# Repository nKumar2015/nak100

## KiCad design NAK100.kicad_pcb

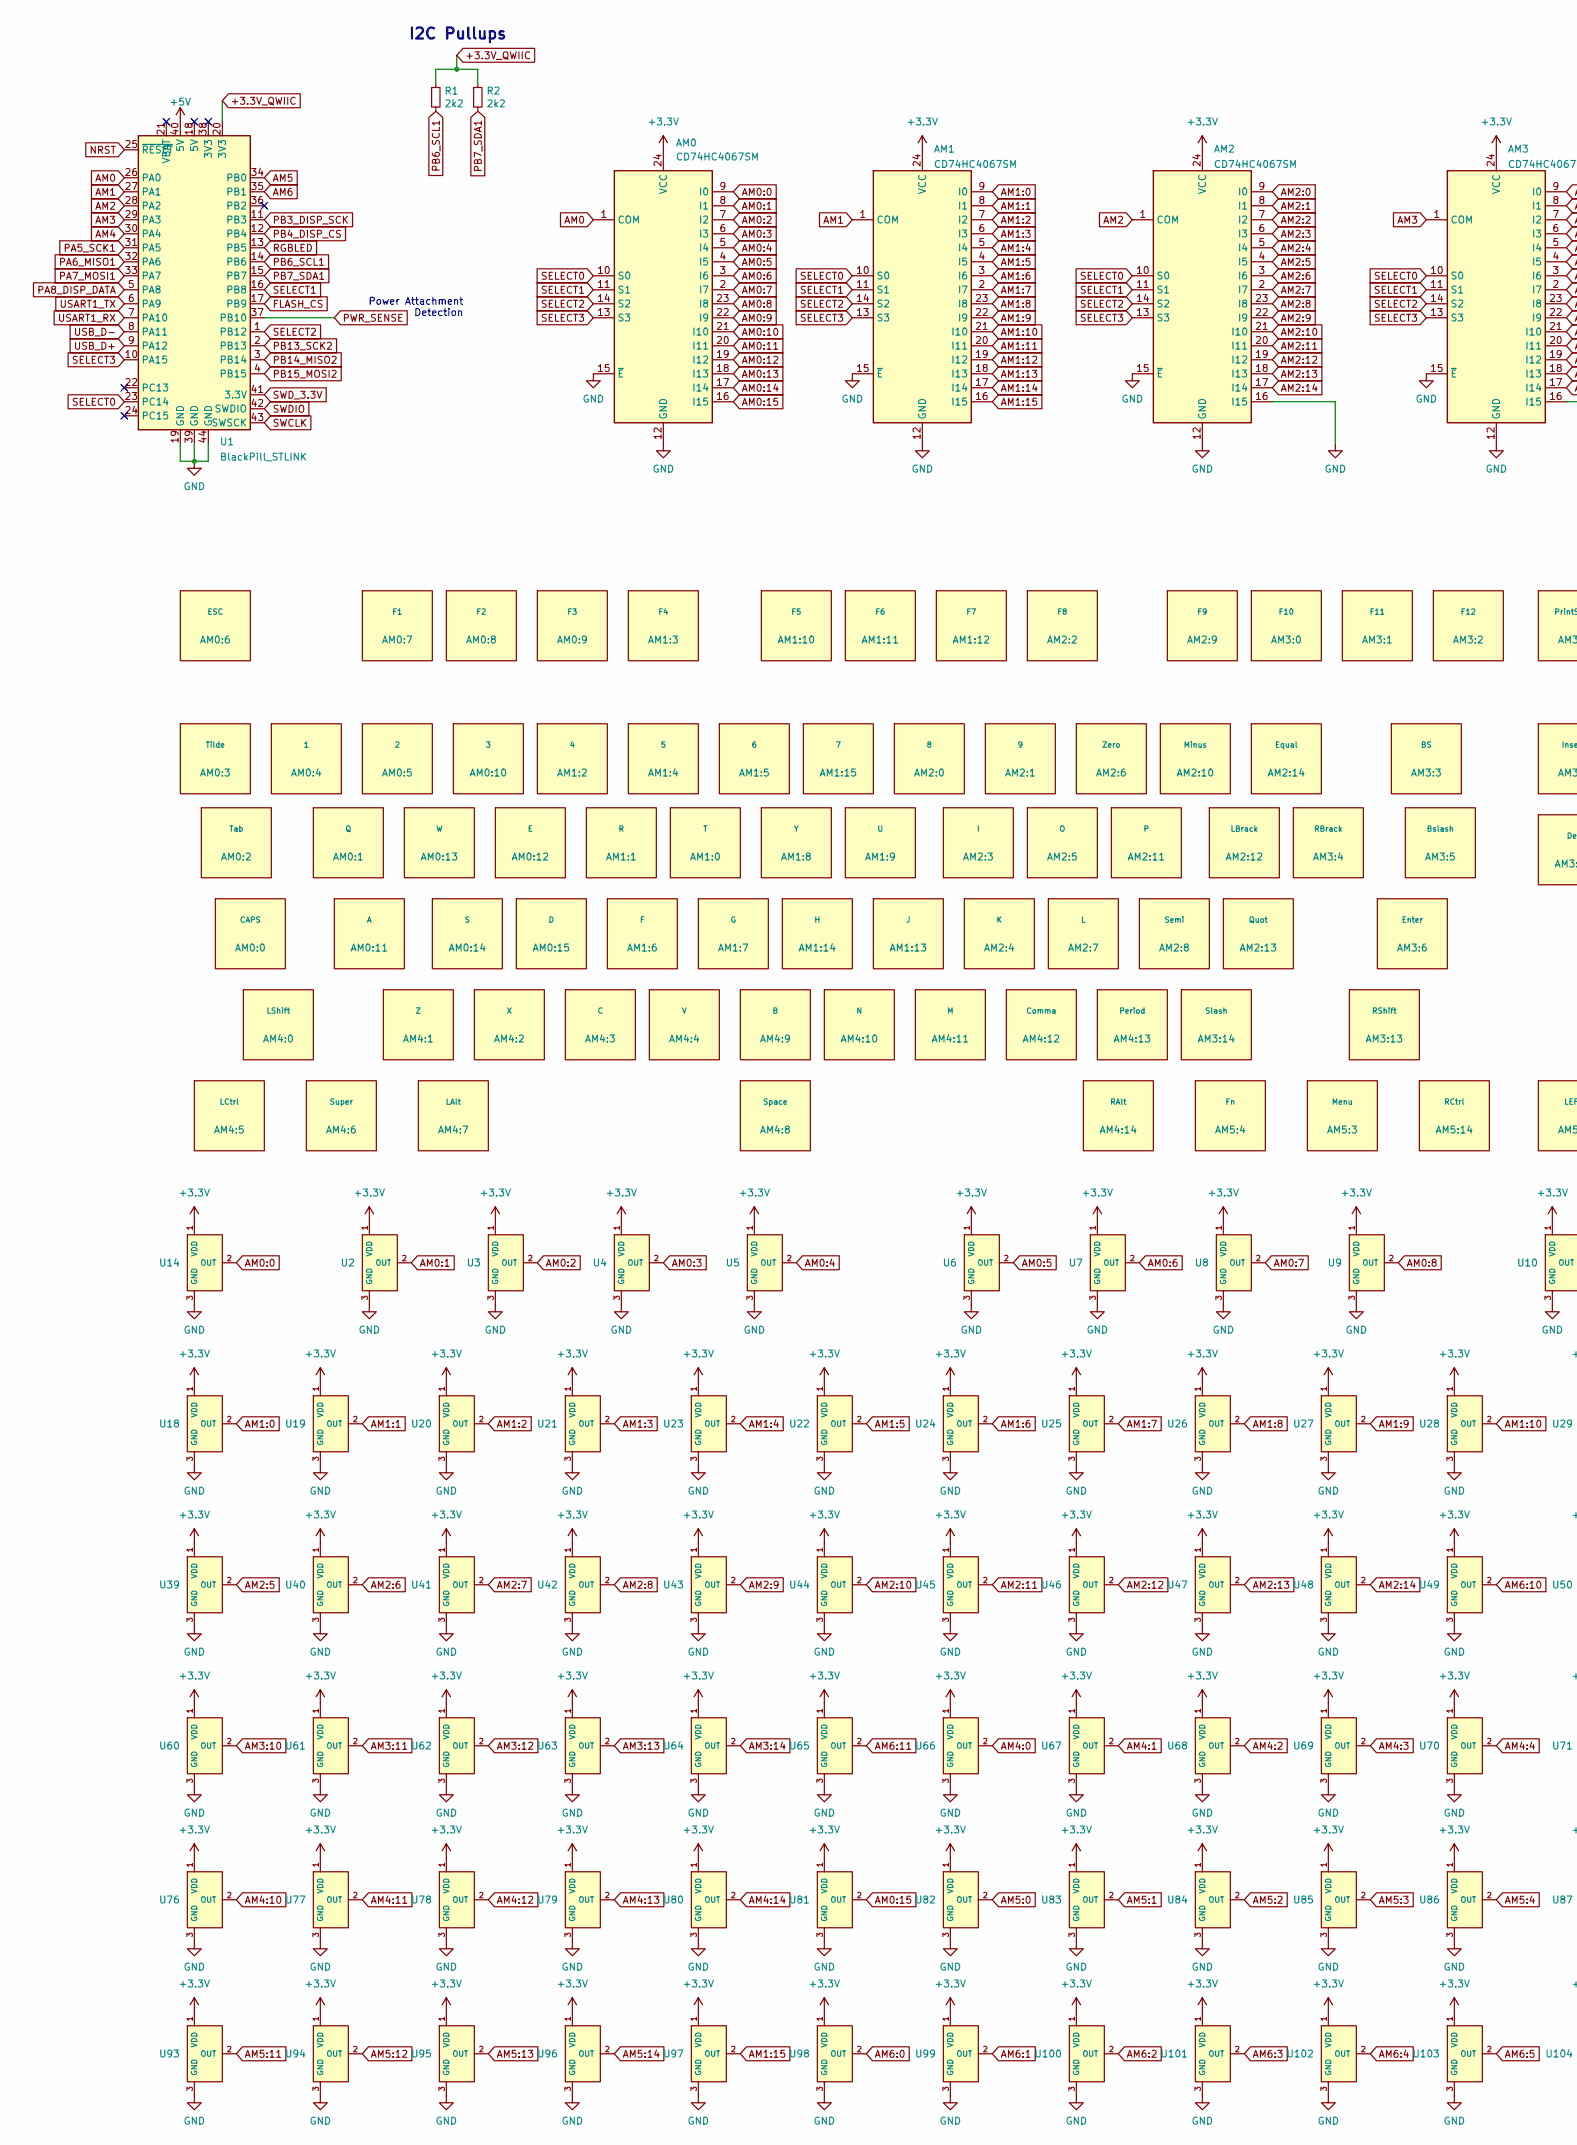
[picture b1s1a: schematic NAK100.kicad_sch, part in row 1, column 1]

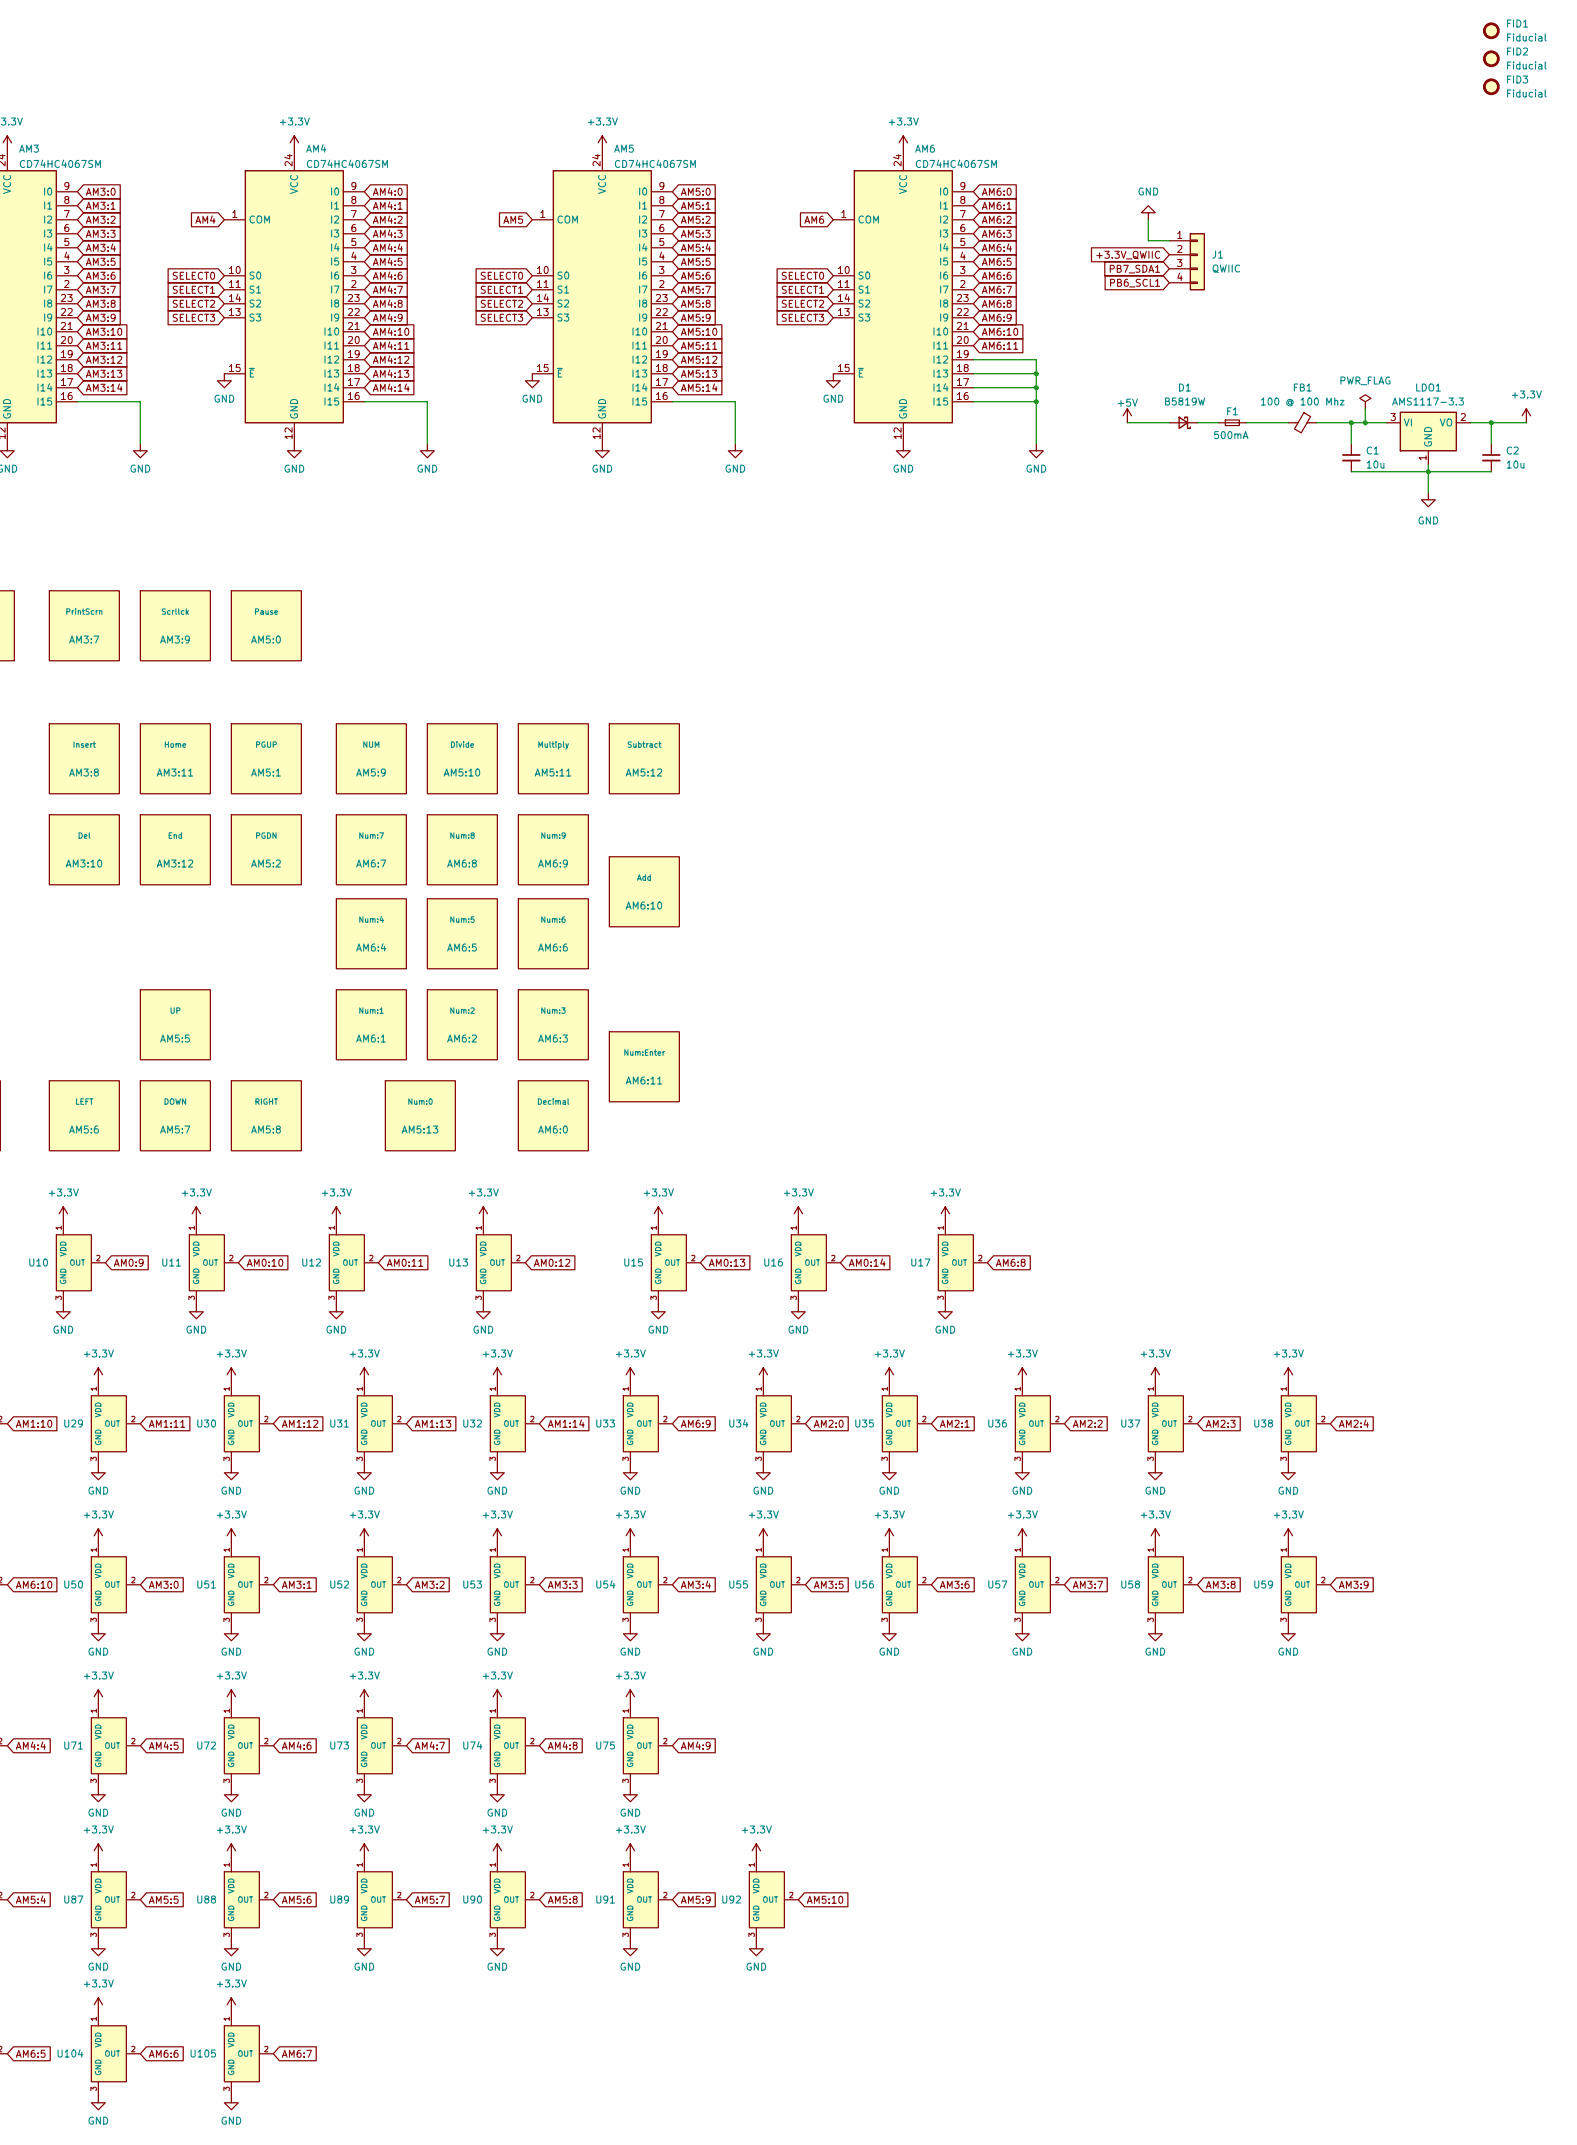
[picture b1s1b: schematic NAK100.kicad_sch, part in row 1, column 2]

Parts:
AM0, AM1, AM2, AM3, AM4, AM5, AM6: CD74HC4067SM; SSOP-24_5.3x8.2mm_P0.65mm; LCSC C98457
AM0:0: CAPS; VoidSwitch_1.75u_SMD
AM0:1: Q; VoidSwitch_1u_SMD
AM0:2: Tab; VoidSwitch_1.5u_SMD
AM0:3: Tilde; VoidSwitch_1u_SMD
AM0:4: 1; VoidSwitch_1u_SMD
AM0:5: 2; VoidSwitch_1u_SMD
AM0:6: ESC; VoidSwitch_1u_SMD
AM0:7: F1; VoidSwitch_1u_SMD
AM0:8: F2; VoidSwitch_1u_SMD
AM0:9: F3; VoidSwitch_1u_SMD
AM0:10: 3; VoidSwitch_1u_SMD
AM0:11: A; VoidSwitch_1u_SMD
AM0:12: E; VoidSwitch_1u_SMD
AM0:13: W; VoidSwitch_1u_SMD
AM0:14: S; VoidSwitch_1u_SMD
AM0:15: D; VoidSwitch_1u_SMD
AM1:0: T; VoidSwitch_1u_SMD
AM1:1: R; VoidSwitch_1u_SMD
AM1:2: 4; VoidSwitch_1u_SMD
AM1:3: F4; VoidSwitch_1u_SMD
AM1:4: 5; VoidSwitch_1u_SMD
AM1:5: 6; VoidSwitch_1u_SMD
AM1:6: F; VoidSwitch_1u_SMD
AM1:7: G; VoidSwitch_1u_SMD
AM1:8: Y; VoidSwitch_1u_SMD
AM1:9: U; VoidSwitch_1u_SMD
AM1:10: F5; VoidSwitch_1u_SMD
AM1:11: F6; VoidSwitch_1u_SMD
AM1:12: F7; VoidSwitch_1u_SMD
AM1:13: J; VoidSwitch_1u_SMD
AM1:14: H; VoidSwitch_1u_SMD
AM1:15: 7; VoidSwitch_1u_SMD
AM2:0: 8; VoidSwitch_1u_SMD
AM2:1: 9; VoidSwitch_1u_SMD
AM2:2: F8; VoidSwitch_1u_SMD
AM2:3: I; VoidSwitch_1u_SMD
AM2:4: K; VoidSwitch_1u_SMD
AM2:5: O; VoidSwitch_1u_SMD
AM2:6: Zero; VoidSwitch_1u_SMD
AM2:7: L; VoidSwitch_1u_SMD
AM2:8: Semi; VoidSwitch_1u_SMD
AM2:9: F9; VoidSwitch_1u_SMD
AM2:10: Minus; VoidSwitch_1u_SMD
AM2:11: P; VoidSwitch_1u_SMD
AM2:12: LBrack; VoidSwitch_1u_SMD
AM2:13: Quot; VoidSwitch_1u_SMD
AM2:14: Equal; VoidSwitch_1u_SMD
AM3:0: F10; VoidSwitch_1u_SMD
AM3:1: F11; VoidSwitch_1u_SMD
AM3:2: F12; VoidSwitch_1u_SMD
AM3:3: BS; VoidSwitch_2u_SMD
AM3:4: RBrack; VoidSwitch_1u_SMD
AM3:5: Bslash; VoidSwitch_1.5u_SMD
AM3:6: Enter; VoidSwitch_2.25u_SMD
AM3:7: PrintScrn; VoidSwitch_1u_SMD
AM3:8: Insert; VoidSwitch_1u_SMD
AM3:9: Scrllck; VoidSwitch_1u_SMD
AM3:10: Del; VoidSwitch_1u_SMD
AM3:11: Home; VoidSwitch_1u_SMD
AM3:12: End; VoidSwitch_1u_SMD
AM3:13: RShift; VoidSwitch_2.75u_SMD
AM3:14: Slash; VoidSwitch_1u_SMD
AM4:0: LShift; VoidSwitch_2.25u_SMD
AM4:1: Z; VoidSwitch_1u_SMD
AM4:2: X; VoidSwitch_1u_SMD
AM4:3: C; VoidSwitch_1u_SMD
AM4:4: V; VoidSwitch_1u_SMD
AM4:5: LCtrl; VoidSwitch_1.25u_SMD
AM4:6: Super; VoidSwitch_1.25u_SMD
AM4:7: LAlt; VoidSwitch_1.25u_SMD
AM4:8: Space; VoidSwitch_6.25u_SMD
AM4:9: B; VoidSwitch_1u_SMD
AM4:10: N; VoidSwitch_1u_SMD
AM4:11: M; VoidSwitch_1u_SMD
AM4:12: Comma; VoidSwitch_1u_SMD
AM4:13: Period; VoidSwitch_1u_SMD
AM4:14: RAlt; VoidSwitch_1.25u_SMD
AM5:0: Pause; VoidSwitch_1u_SMD
AM5:1: PGUP; VoidSwitch_1u_SMD
AM5:2: PGDN; VoidSwitch_1u_SMD
AM5:3: Menu; VoidSwitch_1.25u_SMD
AM5:4: Fn; VoidSwitch_1.25u_SMD
AM5:5: UP; VoidSwitch_1u_SMD
AM5:6: LEFT; VoidSwitch_1u_SMD
AM5:7: DOWN; VoidSwitch_1u_SMD
AM5:8: RIGHT; VoidSwitch_1u_SMD
AM5:9: NUM; VoidSwitch_1u_SMD
AM5:10: Divide; VoidSwitch_1u_SMD
AM5:11: Multiply; VoidSwitch_1u_SMD
AM5:12: Subtract; VoidSwitch_1u_SMD
AM5:13: Num:0; VoidSwitch_2u_SMD
AM5:14: RCtrl; VoidSwitch_1.25u_SMD
AM6:0: Decimal; VoidSwitch_1u_SMD
AM6:1: Num:1; VoidSwitch_1u_SMD
AM6:2: Num:2; VoidSwitch_1u_SMD
AM6:3: Num:3; VoidSwitch_1u_SMD
AM6:4: Num:4; VoidSwitch_1u_SMD
AM6:5: Num:5; VoidSwitch_1u_SMD
AM6:6: Num:6; VoidSwitch_1u_SMD
AM6:7: Num:7; VoidSwitch_1u_SMD
AM6:8: Num:8; VoidSwitch_1u_SMD
AM6:9: Num:9; VoidSwitch_1u_SMD
AM6:10: Add; VoidSwitch_2uv_SMD
AM6:11: Num:Enter; VoidSwitch_2uv_SMD
C1, C2: 10u; C_0402_1005Metric
D1: B5819W; D_SOD-123
F1: 500mA; Fuse_0603_1608Metric
FB1: 100 @ 100 Mhz; L_0805_2012Metric
FID1, FID2, FID3: Fiducial; Fiducial_1mm_Mask2mm
J1: QWIIC; JST_SH_BM04B-SRSS-TB_1x04-1MP_P1.00mm_Vertical
LDO1: AMS1117-3.3; SOT-223-3_TabPin2
R1, R2: 2k2; R_0402_1005Metric; MPN 0402WGF2201TCE; LCSC Part C25879
U1: BlackPill_STLINK
U2, U3, U4, U5, U6, U7, U8, U9, U10, U11, U12, U13, U14, U15, U16, U17, U18, U19, U20, U21, U22, U23, U24, U25, U26, U27, U28, U29, U30, U31, U32, U33, U34, U35, U36, U37, U38, U39, U40, U41, U42, U43, U44, U45, U46, U47, U48, U49, U50, U51, U52, U53, U54, U55, U56, U57, U58, U59, U60, U61, U62, U63, U64, U65, U66, U67, U68, U69, U70, U71, U72, U73, U74, U75, U76, U77, U78, U79, U80, U81, U82, U83, U84, U85, U86, U87, U88, U89, U90, U91, U92, U93, U94, U95, U96, U97, U98, U99, U100, U101, U102, U103, U104, U105: Hall_Sensor; SOT-23; MPN GH39FKSW; LCSC Part C266230

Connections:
+3.3V: AM0.24 (VCC), AM1.24 (VCC), AM2.24 (VCC), AM3.24 (VCC), AM4.24 (VCC), AM5.24 (VCC), AM6.24 (VCC), C2.1, LDO1.2 (VO), U2.1 (VDD), U3.1 (VDD), U4.1 (VDD), U5.1 (VDD), U6.1 (VDD), U7.1 (VDD), U8.1 (VDD), U9.1 (VDD), U10.1 (VDD), U11.1 (VDD), U12.1 (VDD), U13.1 (VDD), U14.1 (VDD), U15.1 (VDD), U16.1 (VDD), U17.1 (VDD), U18.1 (VDD), U19.1 (VDD), U20.1 (VDD), U21.1 (VDD), U22.1 (VDD), U23.1 (VDD), U24.1 (VDD), U25.1 (VDD), U26.1 (VDD), U27.1 (VDD), U28.1 (VDD), U29.1 (VDD), U30.1 (VDD), U31.1 (VDD), U32.1 (VDD), U33.1 (VDD), U34.1 (VDD), U35.1 (VDD), U36.1 (VDD), U37.1 (VDD), U38.1 (VDD), U39.1 (VDD), U40.1 (VDD), U41.1 (VDD), U42.1 (VDD), U43.1 (VDD), U44.1 (VDD), U45.1 (VDD), U46.1 (VDD), U47.1 (VDD), U48.1 (VDD), U49.1 (VDD), U50.1 (VDD), U51.1 (VDD), U52.1 (VDD), U53.1 (VDD), U54.1 (VDD), U55.1 (VDD), U56.1 (VDD), U57.1 (VDD), U58.1 (VDD), U59.1 (VDD), U60.1 (VDD), U61.1 (VDD), U62.1 (VDD), U63.1 (VDD), U64.1 (VDD), U65.1 (VDD), U66.1 (VDD), U67.1 (VDD), U68.1 (VDD), U69.1 (VDD), U70.1 (VDD), U71.1 (VDD), U72.1 (VDD), U73.1 (VDD), U74.1 (VDD), U75.1 (VDD), U76.1 (VDD), U77.1 (VDD), U78.1 (VDD), U79.1 (VDD), U80.1 (VDD), U81.1 (VDD), U82.1 (VDD), U83.1 (VDD), U84.1 (VDD), U85.1 (VDD), U86.1 (VDD), U87.1 (VDD), U88.1 (VDD), U89.1 (VDD), U90.1 (VDD), U91.1 (VDD), U92.1 (VDD), U93.1 (VDD), U94.1 (VDD), U95.1 (VDD), U96.1 (VDD), U97.1 (VDD), U98.1 (VDD), U99.1 (VDD), U100.1 (VDD), U101.1 (VDD), U102.1 (VDD), U103.1 (VDD), U104.1 (VDD), U105.1 (VDD)
+3.3V_QWIIC: J1.2, R1.1, R2.1, U1.20 (3V3)
+5V: D1.2 (A), U1.40 (5V)
AM0: AM0.1 (COM), U1.26 (PA0)
AM0:0: AM0.9 (I0), U14.2 (OUT)
AM0:1: AM0.8 (I1), U2.2 (OUT)
AM0:2: AM0.7 (I2), U3.2 (OUT)
AM0:3: AM0.6 (I3), U4.2 (OUT)
AM0:4: AM0.5 (I4), U5.2 (OUT)
AM0:5: AM0.4 (I5), U6.2 (OUT)
AM0:6: AM0.3 (I6), U7.2 (OUT)
AM0:7: AM0.2 (I7), U8.2 (OUT)
AM0:8: AM0.23 (I8), U9.2 (OUT)
AM0:9: AM0.22 (I9), U10.2 (OUT)
AM0:10: AM0.21 (I10), U11.2 (OUT)
AM0:11: AM0.20 (I11), U12.2 (OUT)
AM0:12: AM0.19 (I12), U13.2 (OUT)
AM0:13: AM0.18 (I13), U15.2 (OUT)
AM0:14: AM0.17 (I14), U16.2 (OUT)
AM0:15: AM0.16 (I15), U81.2 (OUT)
AM1: AM1.1 (COM), U1.27 (PA1)
AM1:0: AM1.9 (I0), U18.2 (OUT)
AM1:1: AM1.8 (I1), U19.2 (OUT)
AM1:2: AM1.7 (I2), U20.2 (OUT)
AM1:3: AM1.6 (I3), U21.2 (OUT)
AM1:4: AM1.5 (I4), U23.2 (OUT)
AM1:5: AM1.4 (I5), U22.2 (OUT)
AM1:6: AM1.3 (I6), U24.2 (OUT)
AM1:7: AM1.2 (I7), U25.2 (OUT)
AM1:8: AM1.23 (I8), U26.2 (OUT)
AM1:9: AM1.22 (I9), U27.2 (OUT)
AM1:10: AM1.21 (I10), U28.2 (OUT)
AM1:11: AM1.20 (I11), U29.2 (OUT)
AM1:12: AM1.19 (I12), U30.2 (OUT)
AM1:13: AM1.18 (I13), U31.2 (OUT)
AM1:14: AM1.17 (I14), U32.2 (OUT)
AM1:15: AM1.16 (I15), U97.2 (OUT)
AM2: AM2.1 (COM), U1.28 (PA2)
AM2:0: AM2.9 (I0), U34.2 (OUT)
AM2:1: AM2.8 (I1), U35.2 (OUT)
AM2:2: AM2.7 (I2), U36.2 (OUT)
AM2:3: AM2.6 (I3), U37.2 (OUT)
AM2:4: AM2.5 (I4), U38.2 (OUT)
AM2:5: AM2.4 (I5), U39.2 (OUT)
AM2:6: AM2.3 (I6), U40.2 (OUT)
AM2:7: AM2.2 (I7), U41.2 (OUT)
AM2:8: AM2.23 (I8), U42.2 (OUT)
AM2:9: AM2.22 (I9), U43.2 (OUT)
AM2:10: AM2.21 (I10), U44.2 (OUT)
AM2:11: AM2.20 (I11), U45.2 (OUT)
AM2:12: AM2.19 (I12), U46.2 (OUT)
AM2:13: AM2.18 (I13), U47.2 (OUT)
AM2:14: AM2.17 (I14), U48.2 (OUT)
AM3: AM3.1 (COM), U1.29 (PA3)
AM3:0: AM3.9 (I0), U50.2 (OUT)
AM3:1: AM3.8 (I1), U51.2 (OUT)
AM3:2: AM3.7 (I2), U52.2 (OUT)
AM3:3: AM3.6 (I3), U53.2 (OUT)
AM3:4: AM3.5 (I4), U54.2 (OUT)
AM3:5: AM3.4 (I5), U55.2 (OUT)
AM3:6: AM3.3 (I6), U56.2 (OUT)
AM3:7: AM3.2 (I7), U57.2 (OUT)
AM3:8: AM3.23 (I8), U58.2 (OUT)
AM3:9: AM3.22 (I9), U59.2 (OUT)
AM3:10: AM3.21 (I10), U60.2 (OUT)
AM3:11: AM3.20 (I11), U61.2 (OUT)
AM3:12: AM3.19 (I12), U62.2 (OUT)
AM3:13: AM3.18 (I13), U63.2 (OUT)
AM3:14: AM3.17 (I14), U64.2 (OUT)
AM4: AM4.1 (COM), U1.30 (PA4)
AM4:0: AM4.9 (I0), U66.2 (OUT)
AM4:1: AM4.8 (I1), U67.2 (OUT)
AM4:2: AM4.7 (I2), U68.2 (OUT)
AM4:3: AM4.6 (I3), U69.2 (OUT)
AM4:4: AM4.5 (I4), U70.2 (OUT)
AM4:5: AM4.4 (I5), U71.2 (OUT)
AM4:6: AM4.3 (I6), U72.2 (OUT)
AM4:7: AM4.2 (I7), U73.2 (OUT)
AM4:8: AM4.23 (I8), U74.2 (OUT)
AM4:9: AM4.22 (I9), U75.2 (OUT)
AM4:10: AM4.21 (I10), U76.2 (OUT)
AM4:11: AM4.20 (I11), U77.2 (OUT)
AM4:12: AM4.19 (I12), U78.2 (OUT)
AM4:13: AM4.18 (I13), U79.2 (OUT)
AM4:14: AM4.17 (I14), U80.2 (OUT)
AM5: AM5.1 (COM), U1.34 (PB0)
AM5:0: AM5.9 (I0), U82.2 (OUT)
AM5:1: AM5.8 (I1), U83.2 (OUT)
AM5:2: AM5.7 (I2), U84.2 (OUT)
AM5:3: AM5.6 (I3), U85.2 (OUT)
AM5:4: AM5.5 (I4), U86.2 (OUT)
AM5:5: AM5.4 (I5), U87.2 (OUT)
AM5:6: AM5.3 (I6), U88.2 (OUT)
AM5:7: AM5.2 (I7), U89.2 (OUT)
AM5:8: AM5.23 (I8), U90.2 (OUT)
AM5:9: AM5.22 (I9), U91.2 (OUT)
AM5:10: AM5.21 (I10), U92.2 (OUT)
AM5:11: AM5.20 (I11), U93.2 (OUT)
AM5:12: AM5.19 (I12), U94.2 (OUT)
AM5:13: AM5.18 (I13), U95.2 (OUT)
AM5:14: AM5.17 (I14), U96.2 (OUT)
AM6: AM6.1 (COM), U1.35 (PB1)
AM6:0: AM6.9 (I0), U98.2 (OUT)
AM6:1: AM6.8 (I1), U99.2 (OUT)
AM6:2: AM6.7 (I2), U100.2 (OUT)
AM6:3: AM6.6 (I3), U101.2 (OUT)
AM6:4: AM6.5 (I4), U102.2 (OUT)
AM6:5: AM6.4 (I5), U103.2 (OUT)
AM6:6: AM6.3 (I6), U104.2 (OUT)
AM6:7: AM6.2 (I7), U105.2 (OUT)
AM6:8: AM6.23 (I8), U17.2 (OUT)
AM6:9: AM6.22 (I9), U33.2 (OUT)
AM6:10: AM6.21 (I10), U49.2 (OUT)
AM6:11: AM6.20 (I11), U65.2 (OUT)
FLASH_CS: U1.17 (PB9)
GND: AM0.12 (GND), AM0.15 (~E), AM1.12 (GND), AM1.15 (~E), AM2.12 (GND), AM2.15 (~E), AM2.16 (I15), AM3.12 (GND), AM3.15 (~E), AM3.16 (I15), AM4.12 (GND), AM4.15 (~E), AM4.16 (I15), AM5.12 (GND), AM5.15 (~E), AM5.16 (I15), AM6.12 (GND), AM6.15 (~E), AM6.16 (I15), AM6.17 (I14), AM6.18 (I13), AM6.19 (I12), C1.2, C2.2, J1.1, LDO1.1 (GND), U1.19 (GND), U1.39 (GND), U1.44 (GND), U2.3 (GND), U3.3 (GND), U4.3 (GND), U5.3 (GND), U6.3 (GND), U7.3 (GND), U8.3 (GND), U9.3 (GND), U10.3 (GND), U11.3 (GND), U12.3 (GND), U13.3 (GND), U14.3 (GND), U15.3 (GND), U16.3 (GND), U17.3 (GND), U18.3 (GND), U19.3 (GND), U20.3 (GND), U21.3 (GND), U22.3 (GND), U23.3 (GND), U24.3 (GND), U25.3 (GND), U26.3 (GND), U27.3 (GND), U28.3 (GND), U29.3 (GND), U30.3 (GND), U31.3 (GND), U32.3 (GND), U33.3 (GND), U34.3 (GND), U35.3 (GND), U36.3 (GND), U37.3 (GND), U38.3 (GND), U39.3 (GND), U40.3 (GND), U41.3 (GND), U42.3 (GND), U43.3 (GND), U44.3 (GND), U45.3 (GND), U46.3 (GND), U47.3 (GND), U48.3 (GND), U49.3 (GND), U50.3 (GND), U51.3 (GND), U52.3 (GND), U53.3 (GND), U54.3 (GND), U55.3 (GND), U56.3 (GND), U57.3 (GND), U58.3 (GND), U59.3 (GND), U60.3 (GND), U61.3 (GND), U62.3 (GND), U63.3 (GND), U64.3 (GND), U65.3 (GND), U66.3 (GND), U67.3 (GND), U68.3 (GND), U69.3 (GND), U70.3 (GND), U71.3 (GND), U72.3 (GND), U73.3 (GND), U74.3 (GND), U75.3 (GND), U76.3 (GND), U77.3 (GND), U78.3 (GND), U79.3 (GND), U80.3 (GND), U81.3 (GND), U82.3 (GND), U83.3 (GND), U84.3 (GND), U85.3 (GND), U86.3 (GND), U87.3 (GND), U88.3 (GND), U89.3 (GND), U90.3 (GND), U91.3 (GND), U92.3 (GND), U93.3 (GND), U94.3 (GND), U95.3 (GND), U96.3 (GND), U97.3 (GND), U98.3 (GND), U99.3 (GND), U100.3 (GND), U101.3 (GND), U102.3 (GND), U103.3 (GND), U104.3 (GND), U105.3 (GND)
NRST: U1.25 (~RESET)
unnamed: D1.1 (K), F1.1
unnamed: F1.2, FB1.2
unnamed: C1.1, FB1.1, LDO1.3 (VI)
PA5_SCK1: U1.31 (PA5)
PA6_MISO1: U1.32 (PA6)
PA7_MOSI1: U1.33 (PA7)
PA8_DISP_DATA: U1.5 (PA8)
PB3_DISP_SCK: U1.11 (PB3)
PB4_DISP_CS: U1.12 (PB4)
PB6_SCL1: J1.4, R1.2, U1.14 (PB6)
PB7_SDA1: J1.3, R2.2, U1.15 (PB7)
PB13_SCK2: U1.2 (PB13)
PB14_MISO2: U1.3 (PB14)
PB15_MOSI2: U1.4 (PB15)
PWR_SENSE: U1.37 (PB10)
RGBLED: U1.13 (PB5)
SELECT0: AM0.10 (S0), AM1.10 (S0), AM2.10 (S0), AM3.10 (S0), AM4.10 (S0), AM5.10 (S0), AM6.10 (S0), U1.23 (PC14)
SELECT1: AM0.11 (S1), AM1.11 (S1), AM2.11 (S1), AM3.11 (S1), AM4.11 (S1), AM5.11 (S1), AM6.11 (S1), U1.16 (PB8)
SELECT2: AM0.14 (S2), AM1.14 (S2), AM2.14 (S2), AM3.14 (S2), AM4.14 (S2), AM5.14 (S2), AM6.14 (S2), U1.1 (PB12)
SELECT3: AM0.13 (S3), AM1.13 (S3), AM2.13 (S3), AM3.13 (S3), AM4.13 (S3), AM5.13 (S3), AM6.13 (S3), U1.10 (PA15)
SWCLK: U1.43 (SWSCK)
SWDIO: U1.42 (SWDIO)
SWD_3.3V: U1.41 (3.3V)
USART1_RX: U1.7 (PA10)
USART1_TX: U1.6 (PA9)
USB_D+: U1.9 (PA12)
USB_D-: U1.8 (PA11)

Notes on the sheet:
Power Attachment Detection
I2C Pullups

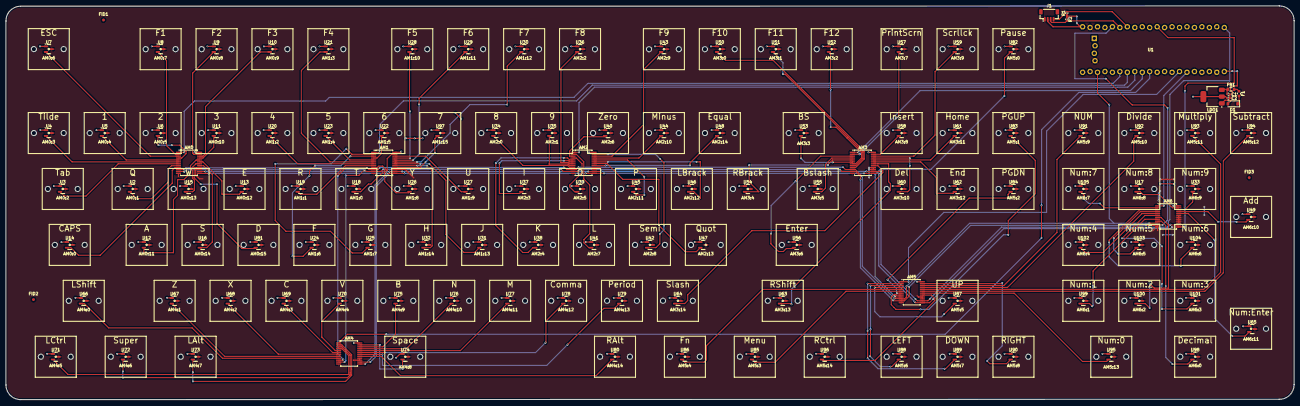
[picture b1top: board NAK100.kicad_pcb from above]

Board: 2 copper layers, 438.8 x 134.1 mm, 228 parts (0 on the bottom side), 124 nets.

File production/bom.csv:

Designator,Footprint,Quantity,Value,LCSC Part #
"AM0, AM1, AM2, AM3, AM4, AM5, AM6",SSOP-24_5.3x8.2mm_P0.65mm,7,CD74HC4067SM,C98457
"C1, C2",0402,2,10u,C15525
D1,D_SOD-123,1,B5819W,C8598
F1,0603,1,500mA,C20789
FB1,0805,1,100 @ 100 Mhz,C1015
J1,JST_SH_BM04B-SRSS-TB_1x04-1MP_P1.00mm_Vertical,1,QWIIC,C160404
LDO1,SOT-223-3_TabPin2,1,AMS1117-3.3,C6186
"R1, R2",0402,2,2k2,C25879
"U10, U100, U101, U102, U103, U104, U105, U11, U12, U13, U14, U15, U16, U17, U18, U19, U2, U20, U21, U22, U23, U24, U25, U26, U27, U28, U29, U3, U30, U31, U32, U33, U34, U35, U36, U37, U38, U39, U4, U40, U41, U42, U43, U44, U45, U46, U47, U48, U49, U5, U50, U51, U52, U53, U54, U55, U56, U57, U58, U59, U6, U60, U61, U62, U63, U64, U65, U66, U67, U68, U69, U7, U70, U71, U72, U73, U74, U75, U76, U77, U78, U79, U8, U80, U81, U82, U83, U84, U85, U86, U87, U88, U89, U9, U90, U91, U92, U93, U94, U95, U96, U97, U98, U99",SOT-23,104,Hall_Sensor,C266230

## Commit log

2025-01-01 inital commit
2025-01-01 update gitignore and removed some files
